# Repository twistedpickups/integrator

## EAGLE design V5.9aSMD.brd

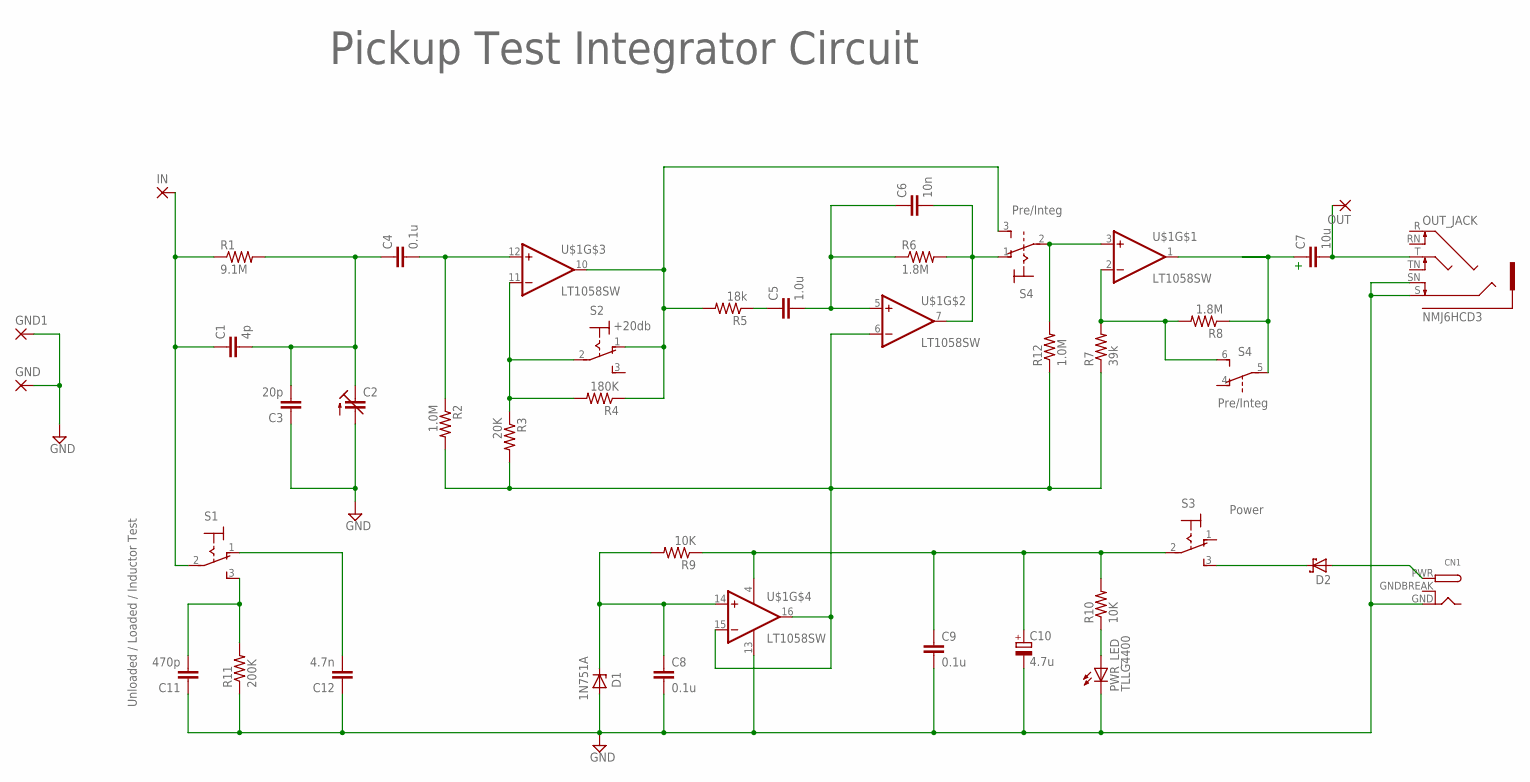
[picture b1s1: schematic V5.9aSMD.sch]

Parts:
C1: 4p; C0805
C2: C-TRIMMGKG20015; GKG20015
C3: 20p; C0805
C4, C8, C9: 0.1u; C0805
C5: 1.0u; C0805
C6: 10n; C0805
C7: 10u; C1206K
C10: 4.7u; A/3216-18R
C11: 470p; C0805
C12: 4.7n; C0805
CN1: DCBARRELPTH; DCJACK_2MM_PTH
D1: ZENER-DIODESOD80C; SOD80C
D2: SCHOTTKY-DIODESMD; SMB
GND, GND1: 2,54/1,1
IN: 2,54/1,1
OUT: 2,54/1,1
OUT_JACK: NMJ6HCD3; AUDIO_JACK_NEUTRIK
PWR_LED: TLLG4400; LED3MM
R1: 9.1M; R0805
R2, R12: 1.0M; R0805
R3: 20K; R0805
R4: 180K; R0805
R5: 18k; R0805
R6, R8: 1.8M; R0805
R7: 39k; R0805
R9, R10: 10K; R0805
R11: 200K; R0805
S1, S2, S3: 320-916
S4: 320-938
U$1: LT1058SW; SO16W

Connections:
GND: C2.1 (A), C3.1, C8.2, C9.2, C10.-, C11.1, C12.1, CN1.GND, D1.A, GND.1, GND1.1, OUT_JACK.S, OUT_JACK.SN, PWR_LED.K (C), R11.1, U$1.13 (V-)
GNDBREAK: CN1.GNDBREAK
IT: C12.2, S1.1 (O)
unnamed: PWR_LED.A, R10.1
unnamed: C5.1, R5.1
unnamed: D2.C, S3.3 (S)
unnamed: R4.1, R5.2, S2.1 (O), S4.3 (S), U$1.10 (OUT)
unnamed: R3.1, R4.2, S2.2, U$1.11 (-IN)
unnamed: C6.2, R6.2, S4.1 (O), U$1.7 (OUT)
unnamed: R7.2, R8.2, S4.6 (S), U$1.2 (-IN)
unnamed: C7.1, R8.1, S4.5, U$1.1 (OUT)
unnamed: C1.2, C2.2 (E), C3.2, C4.1, R1.2
unnamed: C8.1, D1.C, R9.2, U$1.14 (+IN)
unnamed: R12.2, S4.2, U$1.3 (+IN)
unnamed: C4.2, R2.1, U$1.12 (+IN)
unnamed: C1.1, IN.1, R1.1, S1.2
unnamed: R2.2, R3.2, R7.1, R12.1, U$1.6 (-IN), U$1.15 (-IN), U$1.16 (OUT)
unnamed: C9.1, C10.+, R9.1, R10.2, S3.2, U$1.4 (V+)
unnamed: C11.2, R11.2, S1.3 (S)
unnamed: C5.2, C6.1, R6.1, U$1.5 (+IN)
unnamed: CN1.PWR, D2.A
unnamed: C7.2, OUT.1, OUT_JACK.T

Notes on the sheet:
Pickup Test Integrator Circuit
Power
Pre/Integ
+20db
Unloaded / Loaded / Inductor Test

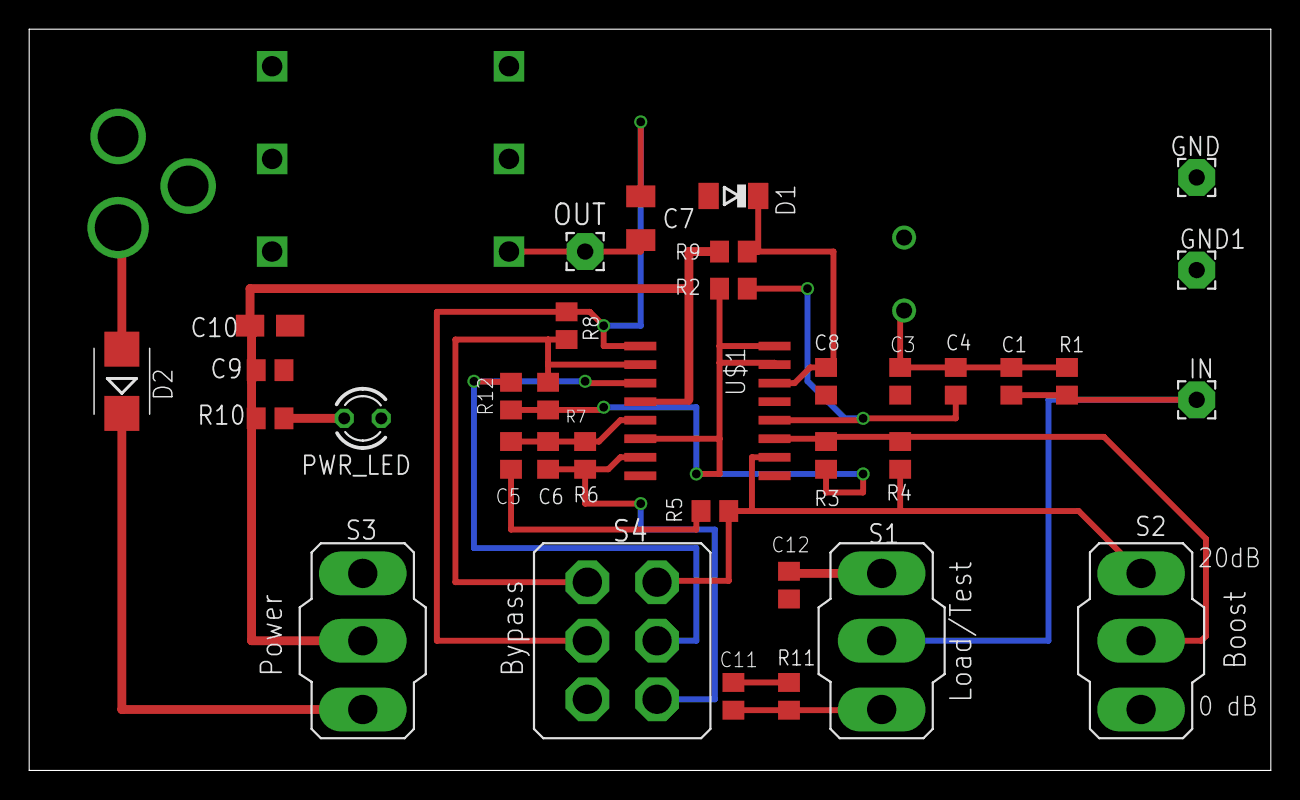
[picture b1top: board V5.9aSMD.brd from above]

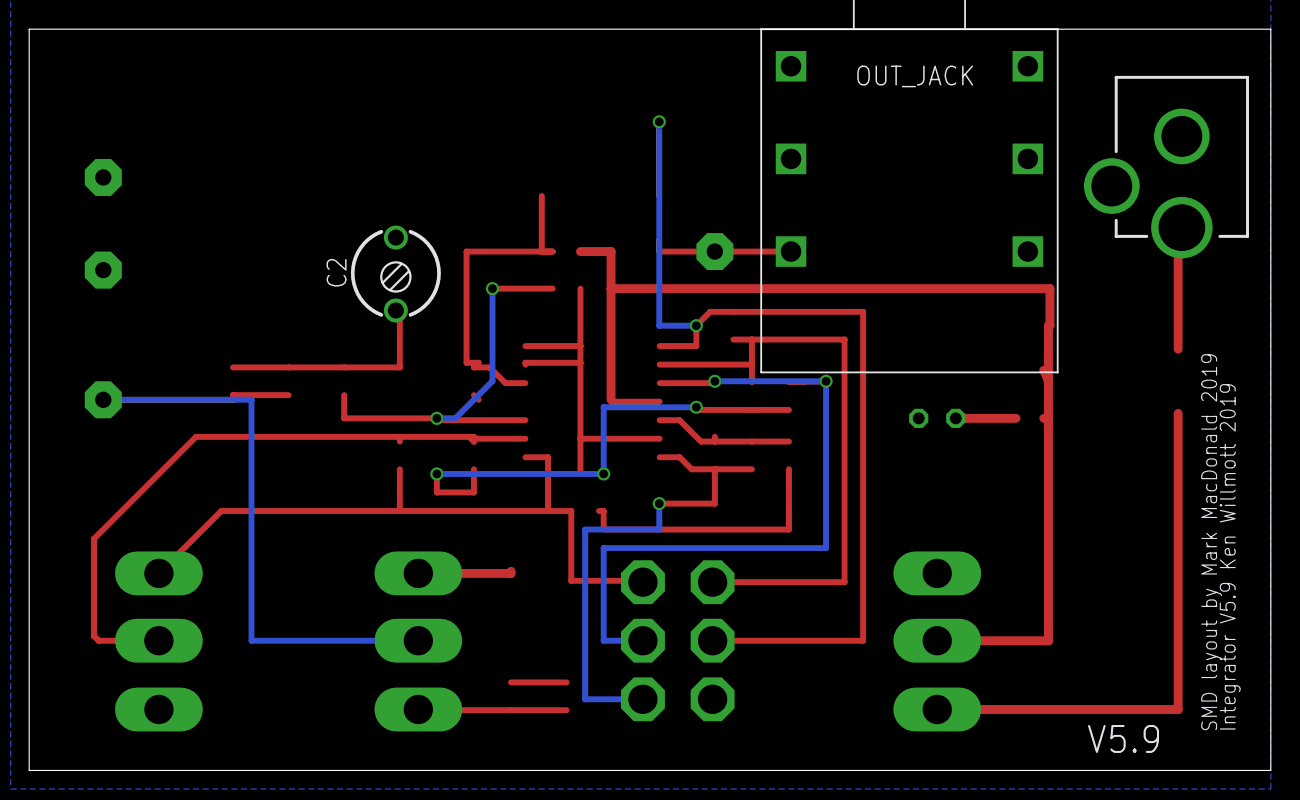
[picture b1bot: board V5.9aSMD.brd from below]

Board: 2 copper layers, 85.1 x 50.8 mm, 38 parts (3 on the bottom side), 21 nets.

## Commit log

2019-09-14 Updated bypass and i/o jacks
2019-09-14 Add files via upload
    Updated board component footprints. Updated BOM for smd and new parts.
2019-09-14 Add files via upload
    Scad file for enclosure mockup and renders
2019-09-15 Production files
